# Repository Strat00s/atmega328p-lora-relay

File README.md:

# atmega328p-lora-relay
Simple atmega based LoRa relay.

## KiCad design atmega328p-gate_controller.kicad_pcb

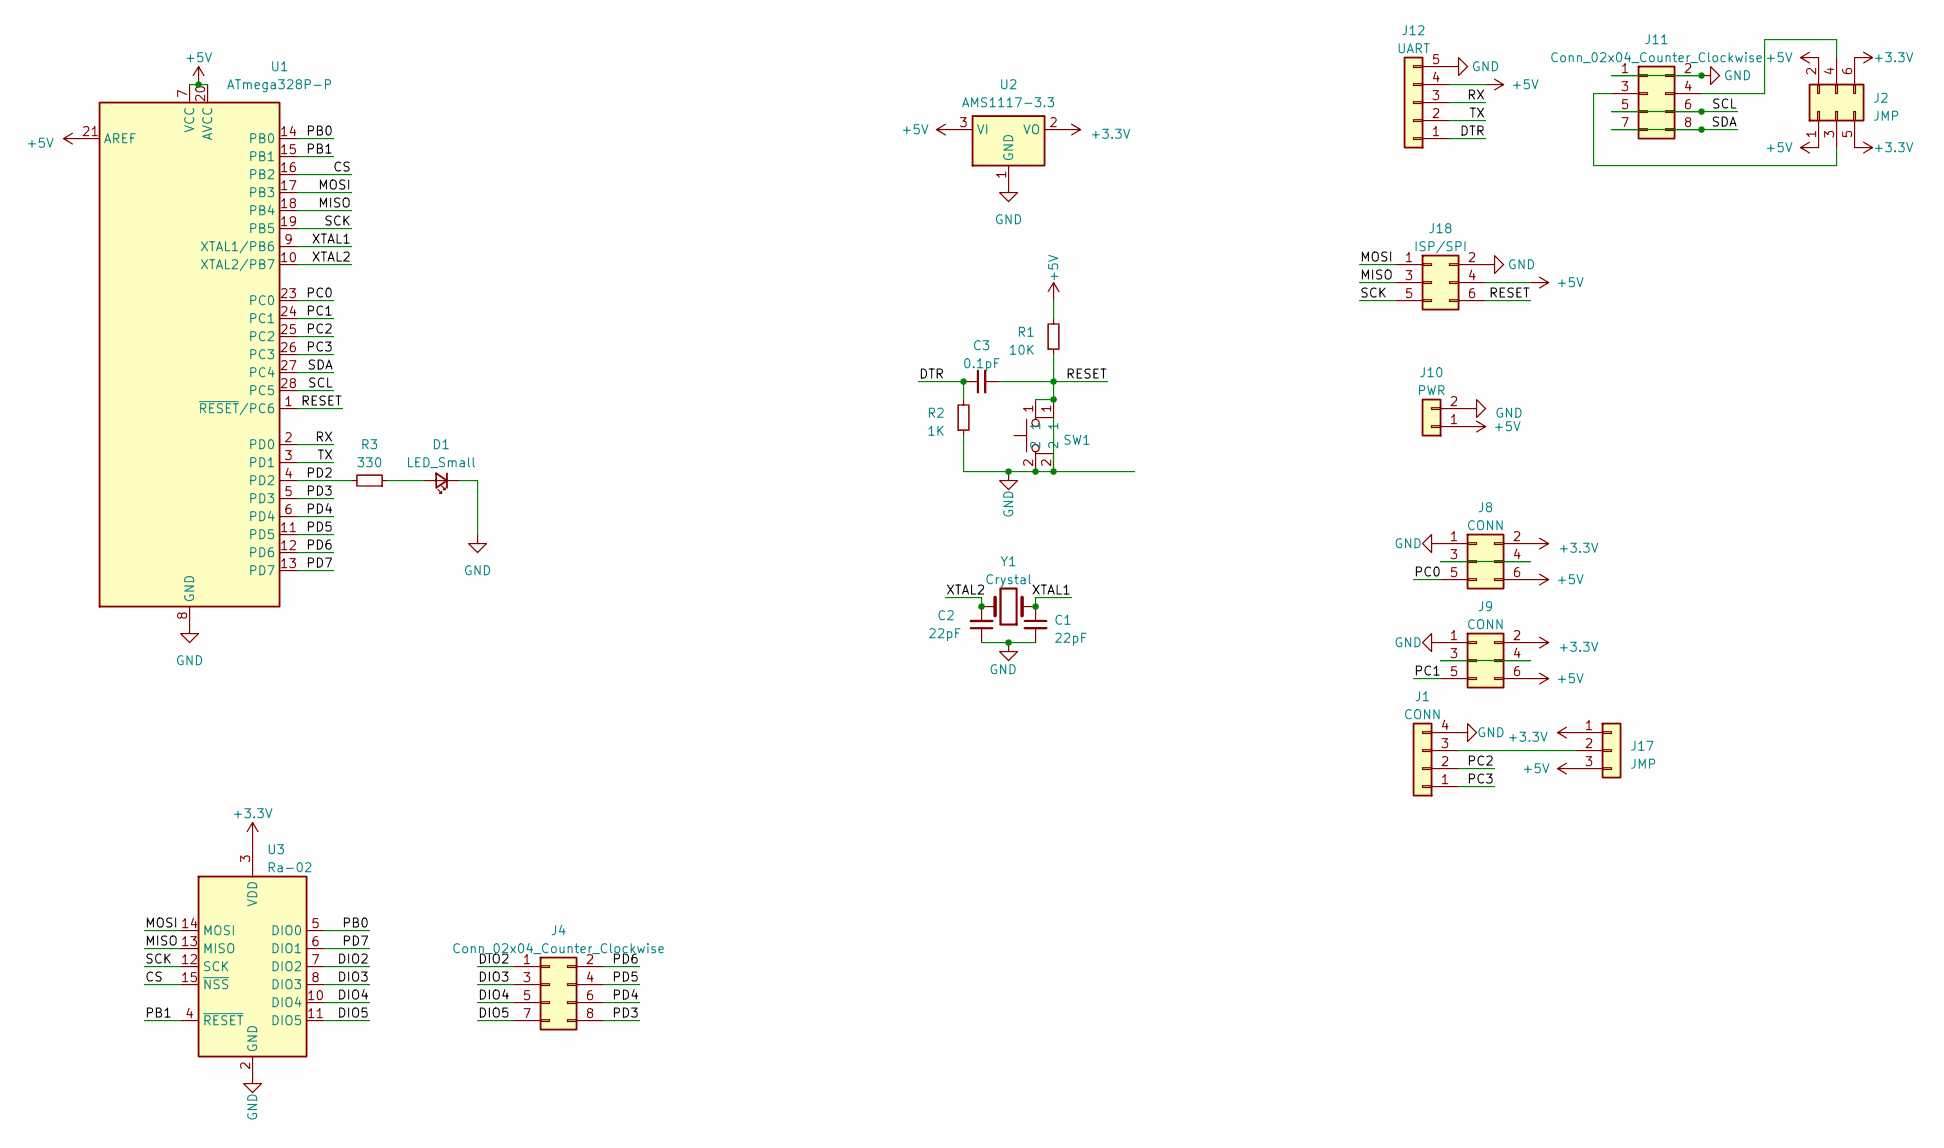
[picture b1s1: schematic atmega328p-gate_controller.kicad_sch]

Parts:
C1, C2: 22pF; C_Disc_D5.0mm_W2.5mm_P2.50mm
C3: 0.1pF; C_Disc_D5.0mm_W2.5mm_P2.50mm
D1: LED_Small; LED_0603_1608Metric_Pad1.05x0.95mm_HandSolder
J1: CONN; PinHeader_1x04_P2.54mm_Vertical
J2: JMP; PinSocket_2x03_P2.54mm_Vertical
J4, J11: Conn_02x04_Counter_Clockwise; PinSocket_2x04_P2.54mm_Vertical
J8, J9: CONN; PinSocket_2x03_P2.54mm_Vertical
J10: PWR; PinHeader_1x02_P2.54mm_Vertical
J12: UART; PinHeader_1x05_P2.54mm_Vertical
J17: JMP; PinHeader_1x03_P2.54mm_Vertical
J18: ISP/SPI; PinSocket_2x03_P2.54mm_Vertical
R1: 10K; R_Axial_DIN0207_L6.3mm_D2.5mm_P10.16mm_Horizontal
R2: 1K; R_Axial_DIN0207_L6.3mm_D2.5mm_P10.16mm_Horizontal
R3: 330; R_0603_1608Metric_Pad0.98x0.95mm_HandSolder
SW1: SW_PUSH_6mm
U1: ATmega328P-P; DIP-28_W7.62mm
U2: AMS1117-3.3; SOT-223-3_TabPin2
U3: Ra-02; Ai-Thinker-Ra-01-LoRa
Y1: Crystal; Crystal_HC49-4H_Vertical

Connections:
+3.3V: J2.5, J2.6, J8.2, J9.2, J17.1, U2.2 (VO), U3.3 (VDD)
+5V: J2.1, J2.2, J8.6, J9.6, J10.1, J12.4, J17.3, J18.4, R1.2, U1.7 (VCC), U1.20 (AVCC), U1.21 (AREF), U2.3 (VI)
/CS: U1.16 (PB2), U3.15 (~NSS)
/DIO2: J4.1, U3.7 (DIO2)
/DIO3: J4.3, U3.8 (DIO3)
/DIO4: J4.5, U3.10 (DIO4)
/DIO5: J4.7, U3.11 (DIO5)
/DTR: C3.1, J12.1, R2.2
/MISO: J18.3, U1.18 (PB4), U3.13 (MISO)
/MOSI: J18.1, U1.17 (PB3), U3.14 (MOSI)
/PB0: U1.14 (PB0), U3.5 (DIO0)
/PB1: U1.15 (PB1), U3.4 (~RESET)
/PC0: J8.5, U1.23 (PC0)
/PC1: J9.5, U1.24 (PC1)
/PC2: J1.2, U1.25 (PC2)
/PC3: J1.1, U1.26 (PC3)
/PD2: R3.2, U1.4 (PD2)
/PD3: J4.8, U1.5 (PD3)
/PD4: J4.6, U1.6 (PD4)
/PD5: J4.4, U1.11 (PD5)
/PD6: J4.2, U1.12 (PD6)
/PD7: U1.13 (PD7), U3.6 (DIO1)
/RESET: C3.2, J18.6, R1.1, SW1.1, U1.1 (~RESET/PC6)
/RX: J12.3, U1.2 (PD0)
/SCK: J18.5, U1.19 (PB5), U3.12 (SCK)
/SCL: J11.5, J11.6, U1.28 (PC5)
/SDA: J11.7, J11.8, U1.27 (PC4)
/TX: J12.2, U1.3 (PD1)
/XTAL1: C1.1, U1.9 (XTAL1/PB6), Y1.1
/XTAL2: C2.2, U1.10 (XTAL2/PB7), Y1.2
GND: C1.2, C2.1, D1.1 (K), J1.4, J8.1, J9.1, J10.2, J11.1, J11.2, J12.5, J18.2, R2.1, SW1.2, U1.8 (GND), U1.22 (GND), U2.1 (GND), U3.1 (GND), U3.2 (GND), U3.9 (GND), U3.16 (GND)
unnamed: D1.2 (A), R3.1
unnamed: J1.3, J17.2
unnamed: J8.3, J8.4
unnamed: J9.3, J9.4
unnamed: J2.3, J11.3
unnamed: J2.4, J11.4

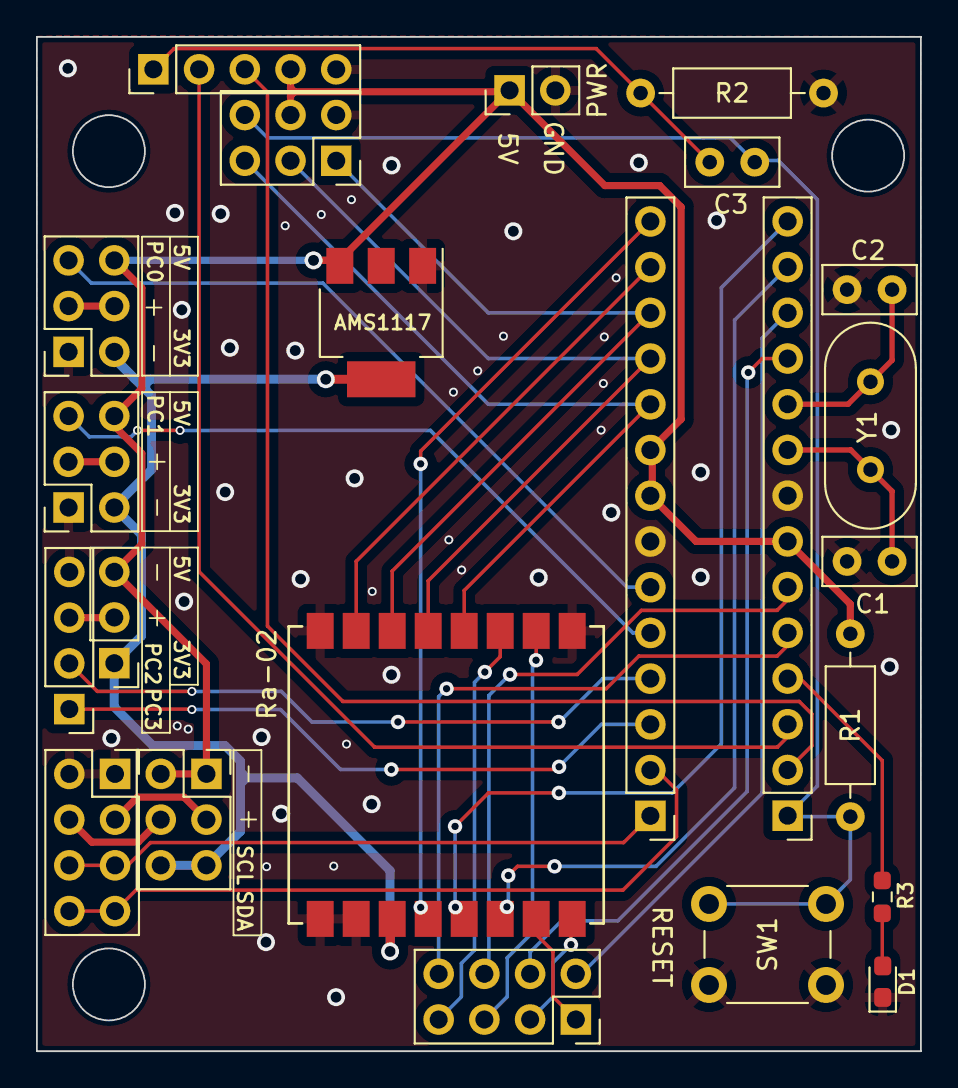
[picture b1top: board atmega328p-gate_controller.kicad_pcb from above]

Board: 2 copper layers, 49.1 x 56.4 mm, 21 parts (0 on the bottom side), 22 nets.

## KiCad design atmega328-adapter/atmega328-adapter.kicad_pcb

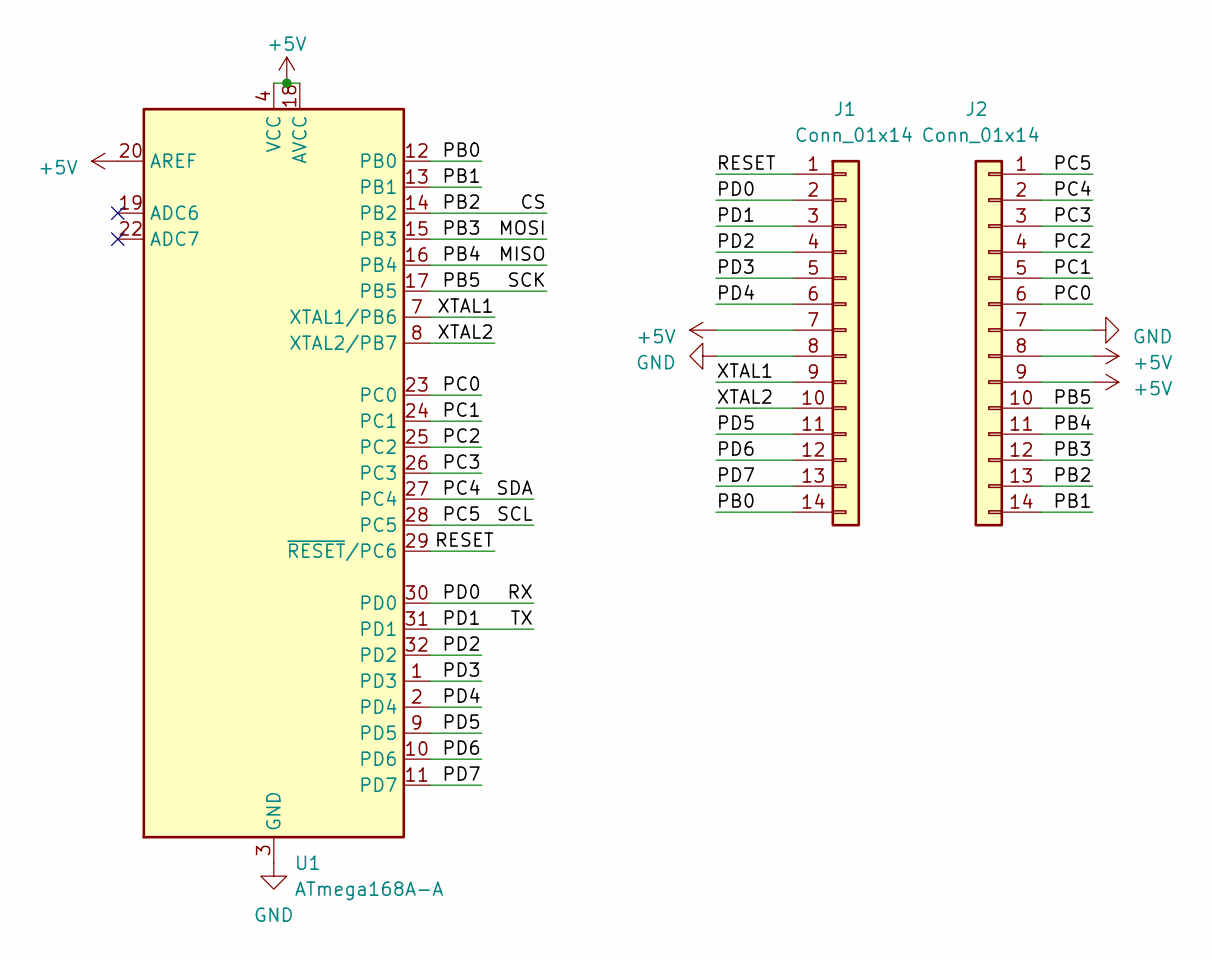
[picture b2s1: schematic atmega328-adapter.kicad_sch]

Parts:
J1, J2: Conn_01x14; PinHeader_1x14_P2.54mm_Vertical
U1: ATmega168A-A; TQFP-32_7x7mm_P0.8mm

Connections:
+5V: J1.7, J2.8, J2.9, U1.4 (VCC), U1.6 (VCC), U1.18 (AVCC), U1.20 (AREF)
/CS: J2.13, U1.14 (PB2)
/MISO: J2.11, U1.16 (PB4)
/MOSI: J2.12, U1.15 (PB3)
/PB0: J1.14, U1.12 (PB0)
/PB1: J2.14, U1.13 (PB1)
/PB5: J2.10, U1.17 (PB5)
/PC0: J2.6, U1.23 (PC0)
/PC1: J2.5, U1.24 (PC1)
/PC2: J2.4, U1.25 (PC2)
/PC3: J2.3, U1.26 (PC3)
/PC4: J2.2, U1.27 (PC4)
/PC5: J2.1, U1.28 (PC5)
/PD0: J1.2, U1.30 (PD0)
/PD1: J1.3, U1.31 (PD1)
/PD2: J1.4, U1.32 (PD2)
/PD3: J1.5, U1.1 (PD3)
/PD4: J1.6, U1.2 (PD4)
/PD5: J1.11, U1.9 (PD5)
/PD6: J1.12, U1.10 (PD6)
/PD7: J1.13, U1.11 (PD7)
/RESET: J1.1, U1.29 (~RESET/PC6)
/XTAL1: J1.9, U1.7 (XTAL1/PB6)
/XTAL2: J1.10, U1.8 (XTAL2/PB7)
GND: J1.8, J2.7, U1.3 (GND), U1.5 (GND), U1.21 (GND)

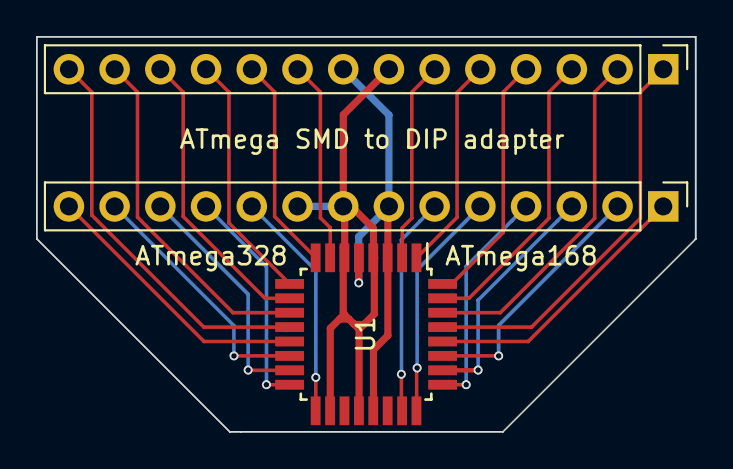
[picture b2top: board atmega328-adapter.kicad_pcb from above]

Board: 2 copper layers, 36.6 x 21.9 mm, 3 parts (0 on the bottom side), 25 nets.

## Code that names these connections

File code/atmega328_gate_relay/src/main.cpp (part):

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#include <avr/wdt.h>
#include "libs/interfaces/lora434InterfaceWrapper.hpp"

#define MISO PIN_PB4
#define MOSI PIN_PB3
#define SCK  PIN_PB5
#define CS   PIN_PB2
#define RST  PIN_PB1
#define DIO0 PIN_PB0

#define STATUS_LED PIN_PD2


/*----(FUNCTION MACROS)----*/
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
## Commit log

2023-07-18 done
2023-07-18 updated adapter
2023-07-19 silkscreen done
2023-07-27 kikit tabs
2023-11-14 simple register packet send
2023-11-15 simple status function
2023-11-23 simple register done
2023-11-24 tinymesh rework(again)
2023-11-24 register works
2023-11-25 mostly done for basic demo
2023-11-26 tm update, simple custom receive only
2023-11-27 it works, don't touch it
2024-01-03 it works?
2024-01-04 last big rework for quite some time
2024-01-17 rework
2024-01-17 fixes
2024-01-17 final changes
